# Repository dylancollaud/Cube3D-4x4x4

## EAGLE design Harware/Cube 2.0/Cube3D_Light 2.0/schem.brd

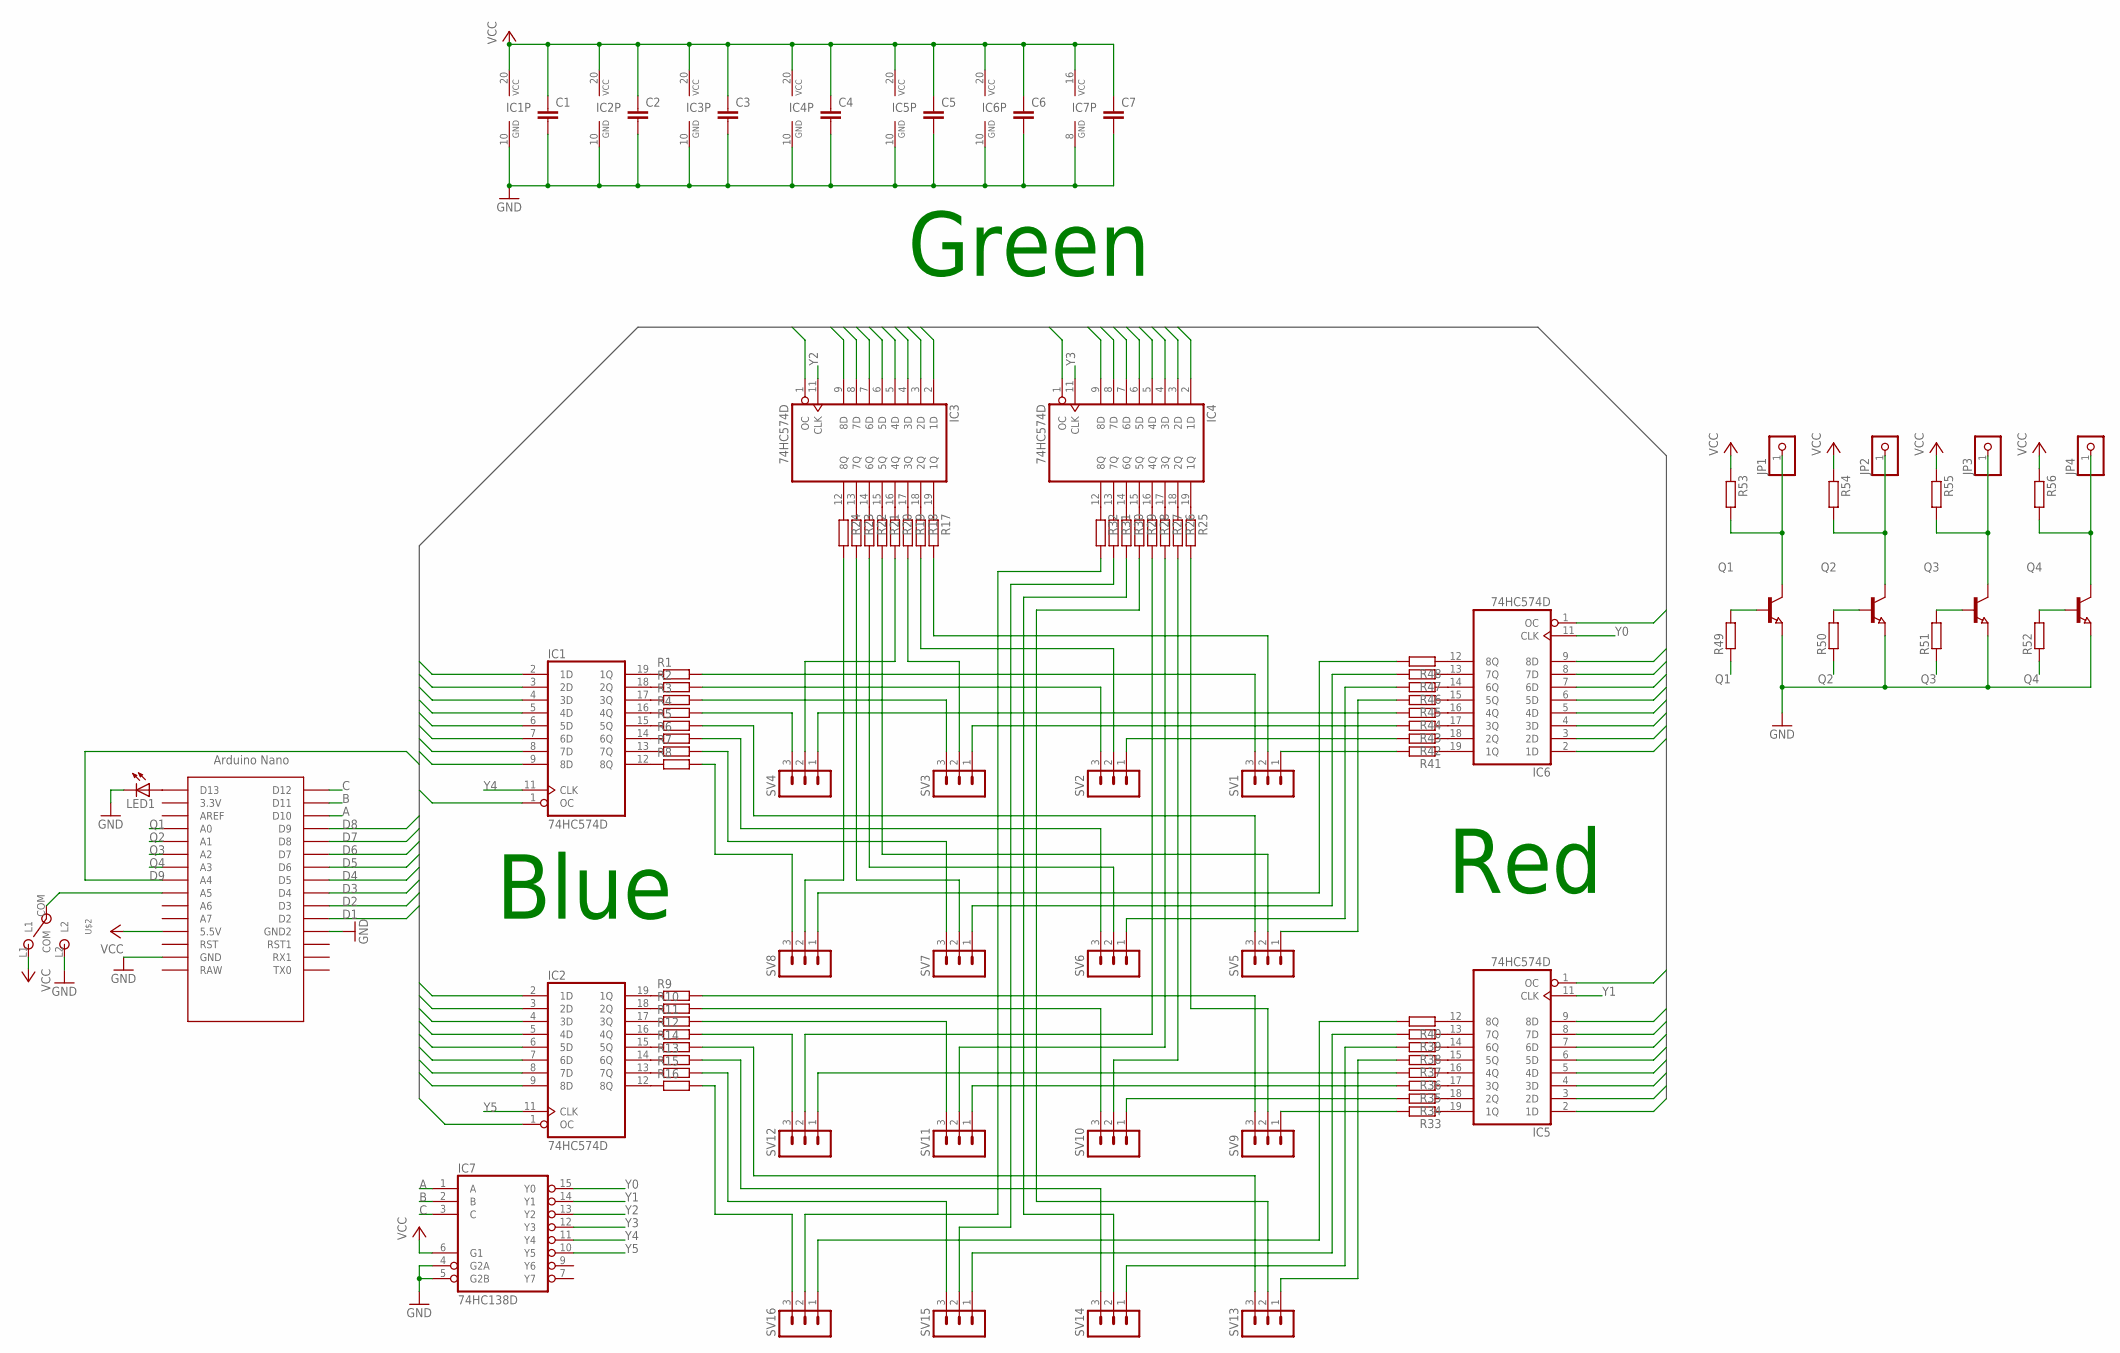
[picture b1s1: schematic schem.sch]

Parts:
C1, C2, C3, C4, C5, C6, C7: C-EUC0805; C0805
IC1, IC2, IC3, IC4, IC5, IC6: 74HC574D; SO20W
IC7: 74HC138D; SO16
JP1, JP2, JP3, JP4: PINHD-1X1; 1X01
LED1: LEDCHIP-LED0805; CHIP-LED0805
Q1, Q2, Q3, Q4: NPN-TRANSISTOR_SOT23; SOT23
R1, R2, R3, R4, R5, R6, R7, R8, R9, R10, R11, R12, R13, R14, R15, R16, R17, R18, R19, R20, R21, R22, R23, R24, R25, R26, R27, R28, R29, R30, R31, R32, R33, R34, R35, R36, R37, R38, R39, R40, R41, R42, R43, R44, R45, R46, R47, R48, R49, R50, R51, R52, R53, R54, R55, R56: R-EU_R0805; R0805
SV1, SV2, SV3, SV4, SV5, SV6, SV7, SV8, SV9, SV10, SV11, SV12, SV13, SV14, SV15, SV16: MA03-1
U$1: NANO
U$2: MSK-12C02_SMD_SPDT_SWITCH; MSK-12C02

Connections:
A: IC7.1 (A), U$1.D10
B: IC7.2 (B), U$1.D11
C: IC7.3 (C), U$1.D12
D1: IC1.2 (1D), IC2.2 (1D), IC3.2 (1D), IC4.2 (1D), IC5.2 (1D), IC6.2 (1D), U$1.D2
D2: IC1.3 (2D), IC2.3 (2D), IC3.3 (2D), IC4.3 (2D), IC5.3 (2D), IC6.3 (2D), U$1.D3
D3: IC1.4 (3D), IC2.4 (3D), IC3.4 (3D), IC4.4 (3D), IC5.4 (3D), IC6.4 (3D), U$1.D4
D4: IC1.5 (4D), IC2.5 (4D), IC3.5 (4D), IC4.5 (4D), IC5.5 (4D), IC6.5 (4D), U$1.D5
D5: IC1.6 (5D), IC2.6 (5D), IC3.6 (5D), IC4.6 (5D), IC5.6 (5D), IC6.6 (5D), U$1.D6
D6: IC1.7 (6D), IC2.7 (6D), IC3.7 (6D), IC4.7 (6D), IC5.7 (6D), IC6.7 (6D), U$1.D7
D7: IC1.8 (7D), IC2.8 (7D), IC3.8 (7D), IC4.8 (7D), IC5.8 (7D), IC6.8 (7D), U$1.D8
D8: IC1.9 (8D), IC2.9 (8D), IC3.9 (8D), IC4.9 (8D), IC5.9 (8D), IC6.9 (8D), U$1.D9
D9: IC1.1 (OC), IC2.1 (OC), IC3.1 (OC), IC4.1 (OC), IC5.1 (OC), IC6.1 (OC), U$1.A4
GND: C1.2, C2.2, C3.2, C4.2, C5.2, C6.2, C7.2, IC1.10 (GND), IC2.10 (GND), IC3.10 (GND), IC4.10 (GND), IC5.10 (GND), IC6.10 (GND), IC7.4 (G2A), IC7.5 (G2B), IC7.8 (GND), LED1.C, Q1.2 (E), Q2.2 (E), Q3.2 (E), Q4.2 (E), U$1.GND, U$1.GND1 (GND2), U$2.L2
unnamed: IC1.19 (1Q), R1.1
unnamed: IC1.18 (2Q), R2.1
unnamed: IC1.17 (3Q), R3.1
unnamed: IC1.16 (4Q), R4.1
unnamed: IC1.15 (5Q), R5.1
unnamed: IC1.14 (6Q), R6.1
unnamed: IC1.13 (7Q), R7.1
unnamed: IC1.12 (8Q), R8.1
unnamed: IC2.19 (1Q), R9.1
unnamed: IC2.18 (2Q), R10.1
unnamed: IC2.17 (3Q), R11.1
unnamed: IC2.16 (4Q), R12.1
unnamed: IC2.14 (6Q), R13.1
unnamed: IC2.15 (5Q), R14.1
unnamed: IC2.13 (7Q), R15.1
unnamed: IC2.12 (8Q), R16.1
unnamed: IC3.19 (1Q), R17.1
unnamed: IC3.18 (2Q), R18.1
unnamed: IC3.17 (3Q), R19.1
unnamed: IC3.16 (4Q), R20.1
unnamed: IC3.15 (5Q), R21.1
unnamed: IC3.14 (6Q), R22.1
unnamed: IC3.13 (7Q), R23.1
unnamed: IC3.12 (8Q), R24.1
unnamed: IC4.19 (1Q), R25.1
unnamed: IC4.18 (2Q), R26.1
unnamed: IC4.17 (3Q), R27.1
unnamed: IC4.16 (4Q), R28.1
unnamed: IC4.15 (5Q), R29.1
unnamed: IC4.14 (6Q), R30.1
unnamed: IC4.13 (7Q), R31.1
unnamed: IC4.12 (8Q), R32.1
unnamed: IC5.19 (1Q), R33.1
unnamed: IC5.18 (2Q), R34.1
unnamed: IC5.17 (3Q), R35.1
unnamed: IC5.16 (4Q), R36.1
unnamed: IC5.15 (5Q), R37.1
unnamed: IC5.14 (6Q), R38.1
unnamed: IC5.13 (7Q), R39.1
unnamed: IC5.12 (8Q), R40.1
unnamed: IC6.19 (1Q), R41.1
unnamed: IC6.18 (2Q), R42.1
unnamed: IC6.17 (3Q), R43.1
unnamed: IC6.16 (4Q), R44.1
unnamed: IC6.15 (5Q), R45.1
unnamed: IC6.14 (6Q), R46.1
unnamed: IC6.13 (7Q), R47.1
unnamed: IC6.12 (8Q), R48.1
unnamed: R1.2, SV1.3
unnamed: R2.2, SV2.3
unnamed: R3.2, SV3.3
unnamed: R4.2, SV4.3
unnamed: R5.2, SV5.3
unnamed: R6.2, SV6.3
unnamed: R7.2, SV7.3
unnamed: R8.2, SV8.3
unnamed: R17.2, SV1.2
unnamed: R18.2, SV2.2
unnamed: R19.2, SV3.2
unnamed: R20.2, SV4.2
unnamed: R21.2, SV5.2
unnamed: R22.2, SV6.2
unnamed: R23.2, SV7.2
unnamed: R24.2, SV8.2
unnamed: R44.2, SV4.1
unnamed: R43.2, SV3.1
unnamed: R42.2, SV2.1
unnamed: R41.2, SV1.1
unnamed: R48.2, SV8.1
unnamed: R9.2, SV9.3
unnamed: R47.2, SV7.1
unnamed: R46.2, SV6.1
unnamed: R45.2, SV5.1
unnamed: R10.2, SV10.3
unnamed: R11.2, SV11.3
unnamed: R12.2, SV12.3
unnamed: R28.2, SV12.2
unnamed: R27.2, SV11.2
unnamed: R26.2, SV10.2
unnamed: R25.2, SV9.2
unnamed: R36.2, SV12.1
unnamed: R35.2, SV11.1
unnamed: R34.2, SV10.1
unnamed: R33.2, SV9.1
unnamed: R14.2, SV13.3
unnamed: R13.2, SV14.3
unnamed: R15.2, SV15.3
unnamed: R16.2, SV16.3
unnamed: R32.2, SV16.2
unnamed: R31.2, SV15.2
unnamed: R30.2, SV14.2
unnamed: R29.2, SV13.2
unnamed: R40.2, SV16.1
unnamed: R39.2, SV15.1
unnamed: R38.2, SV14.1
unnamed: R37.2, SV13.1
unnamed: U$1.A5, U$2.COM
unnamed: JP1.1, Q1.3 (C), R53.2
unnamed: JP2.1, Q2.3 (C), R54.2
unnamed: JP3.1, Q3.3 (C), R55.2
unnamed: JP4.1, Q4.3 (C), R56.2
unnamed: Q1.1 (B), R49.2
unnamed: Q2.1 (B), R50.2
unnamed: Q3.1 (B), R51.2
unnamed: Q4.1 (B), R52.2
unnamed: LED1.A, U$1.D13
Q1: R49.1, U$1.A0
Q2: R50.1, U$1.A1
Q3: R51.1, U$1.A2
Q4: R52.1, U$1.A3
VCC: C1.1, C2.1, C3.1, C4.1, C5.1, C6.1, C7.1, IC1.20 (VCC), IC2.20 (VCC), IC3.20 (VCC), IC4.20 (VCC), IC5.20 (VCC), IC6.20 (VCC), IC7.6 (G1), IC7.16 (VCC), R53.1, R54.1, R55.1, R56.1, U$1.5V (5.5V), U$2.L1
Y0: IC6.11 (CLK), IC7.15 (Y0)
Y1: IC5.11 (CLK), IC7.14 (Y1)
Y2: IC3.11 (CLK), IC7.13 (Y2)
Y3: IC4.11 (CLK), IC7.12 (Y3)
Y4: IC1.11 (CLK), IC7.11 (Y4)
Y5: IC2.11 (CLK), IC7.10 (Y5)

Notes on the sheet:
Red
Green
Blue

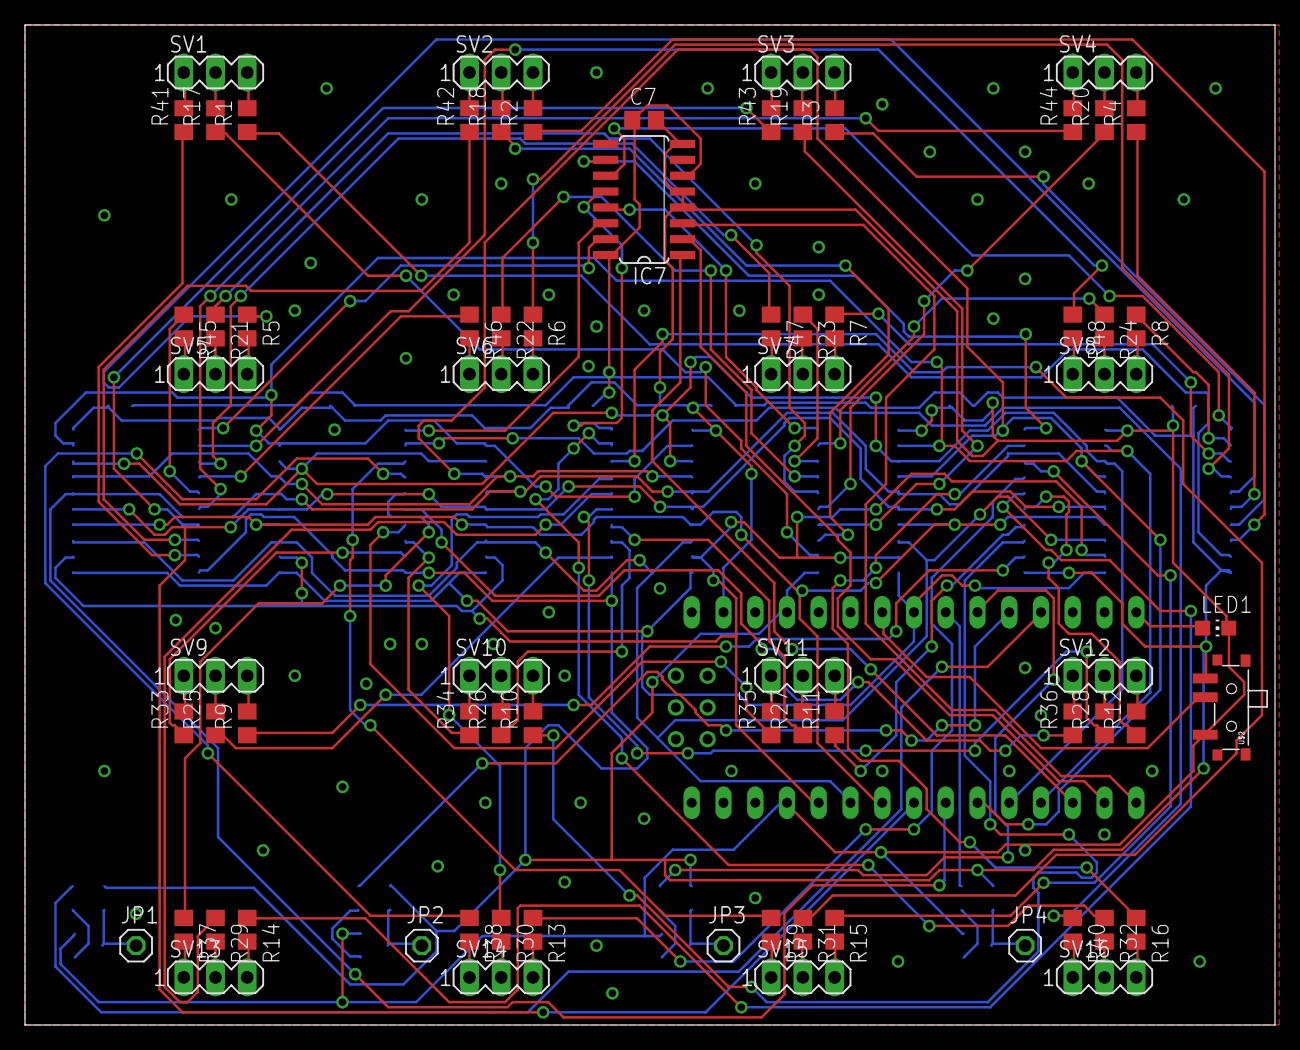
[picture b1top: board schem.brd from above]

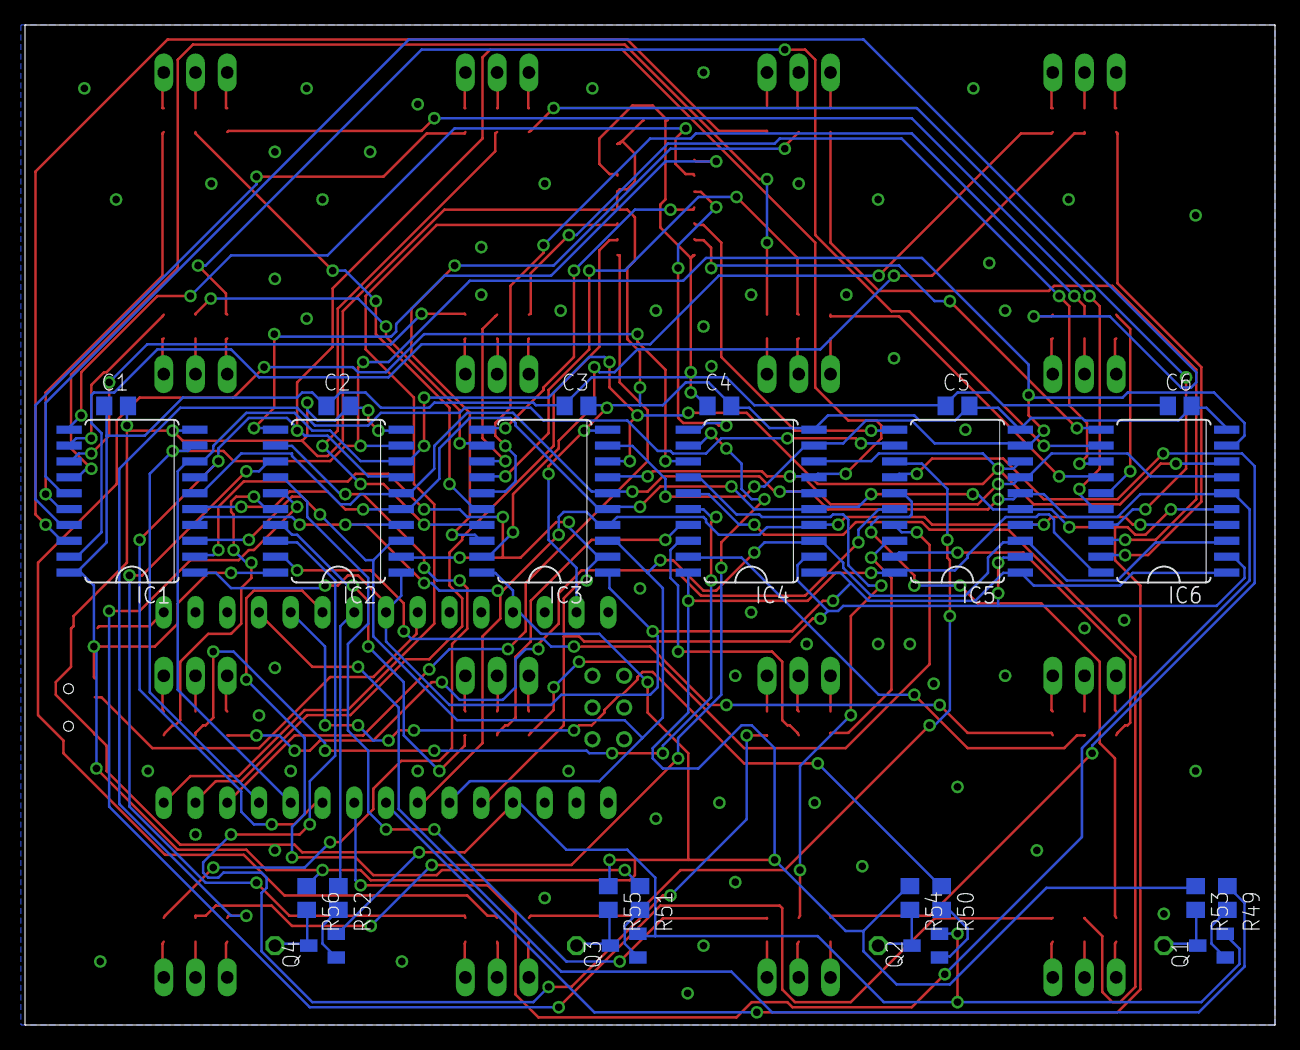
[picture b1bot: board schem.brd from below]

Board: 2 copper layers, 100.0 x 80.0 mm, 97 parts (24 on the bottom side), 130 nets.

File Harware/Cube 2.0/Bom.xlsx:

Reference | Qty | Value | DNP | Digikey | Footprint | Datasheet
C1,C2,C3,C4,C5,C6,C7 | 7 | 100n |  |  | schem:C0805
IC1,IC2,IC3,IC4,IC5,IC6 | 6 | 74hc574d |  | 1727-74HC574D-Q100,118CT-ND | schem:SO20W
IC7 | 1 | 74HC138D |  | 74HC138DCT-ND | schem:SO16
JP1,JP2,JP3,JP4 | 4 |  |  |  | schem:1X01
LED1 | 1 | LEDCHIP-LED0805 |  |  | schem:CHIP-LED0805
Q1,Q2,Q3,Q4 | 4 | NPN-TRANSISTOR_SOT23 |  |  | schem:SOT23
R1,R2,R3,R4,R5,R6,R7,R8,R9,R10,R11,R12,R13,R14,R15,R16,R17,R18,R19,R20,R21,R22,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 | 56 | Selon LED (RGB) ~100 à 300 ohm |  |  | schem:R0805
SV1,SV2,SV3,SV4,SV5,SV6,SV7,SV8,SV9,SV10,SV11,SV12,SV13,SV14,SV15,SV16 | 16 |  |  |  | schem:MA03-1
U$1 | 1 | Arduino NANO (PIN REVERSE SIDE) |  |  | schem:NANO
U$2 | 1 | MSK-12C02_SMD_SPDT_SWITCH |  |  | schem:MSK-12C02

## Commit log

2016-10-04 :lollipop: Added .gitattributes & .gitignore files
2016-10-04 V 0.1 First Update
    Not all are implemented
2016-10-04 Revert "V 0.1 First Update"
    This reverts commit a9ef25d9200d1bd5a5e40bdbc2a6f6c1de7be3a8.
2016-10-04 StartVersion
2016-10-06 Ajout des shémas Eagle
2016-10-06 Photos et vidéo de la version 1.0
2016-10-08 Add Rainbow Fonction
2016-10-15 CardBoard V2 new implementation
    Alpha level to 32 bit
2016-10-15 Add new Fonction RainbowVertical & On Axis
2026-06-04 Add Bom
